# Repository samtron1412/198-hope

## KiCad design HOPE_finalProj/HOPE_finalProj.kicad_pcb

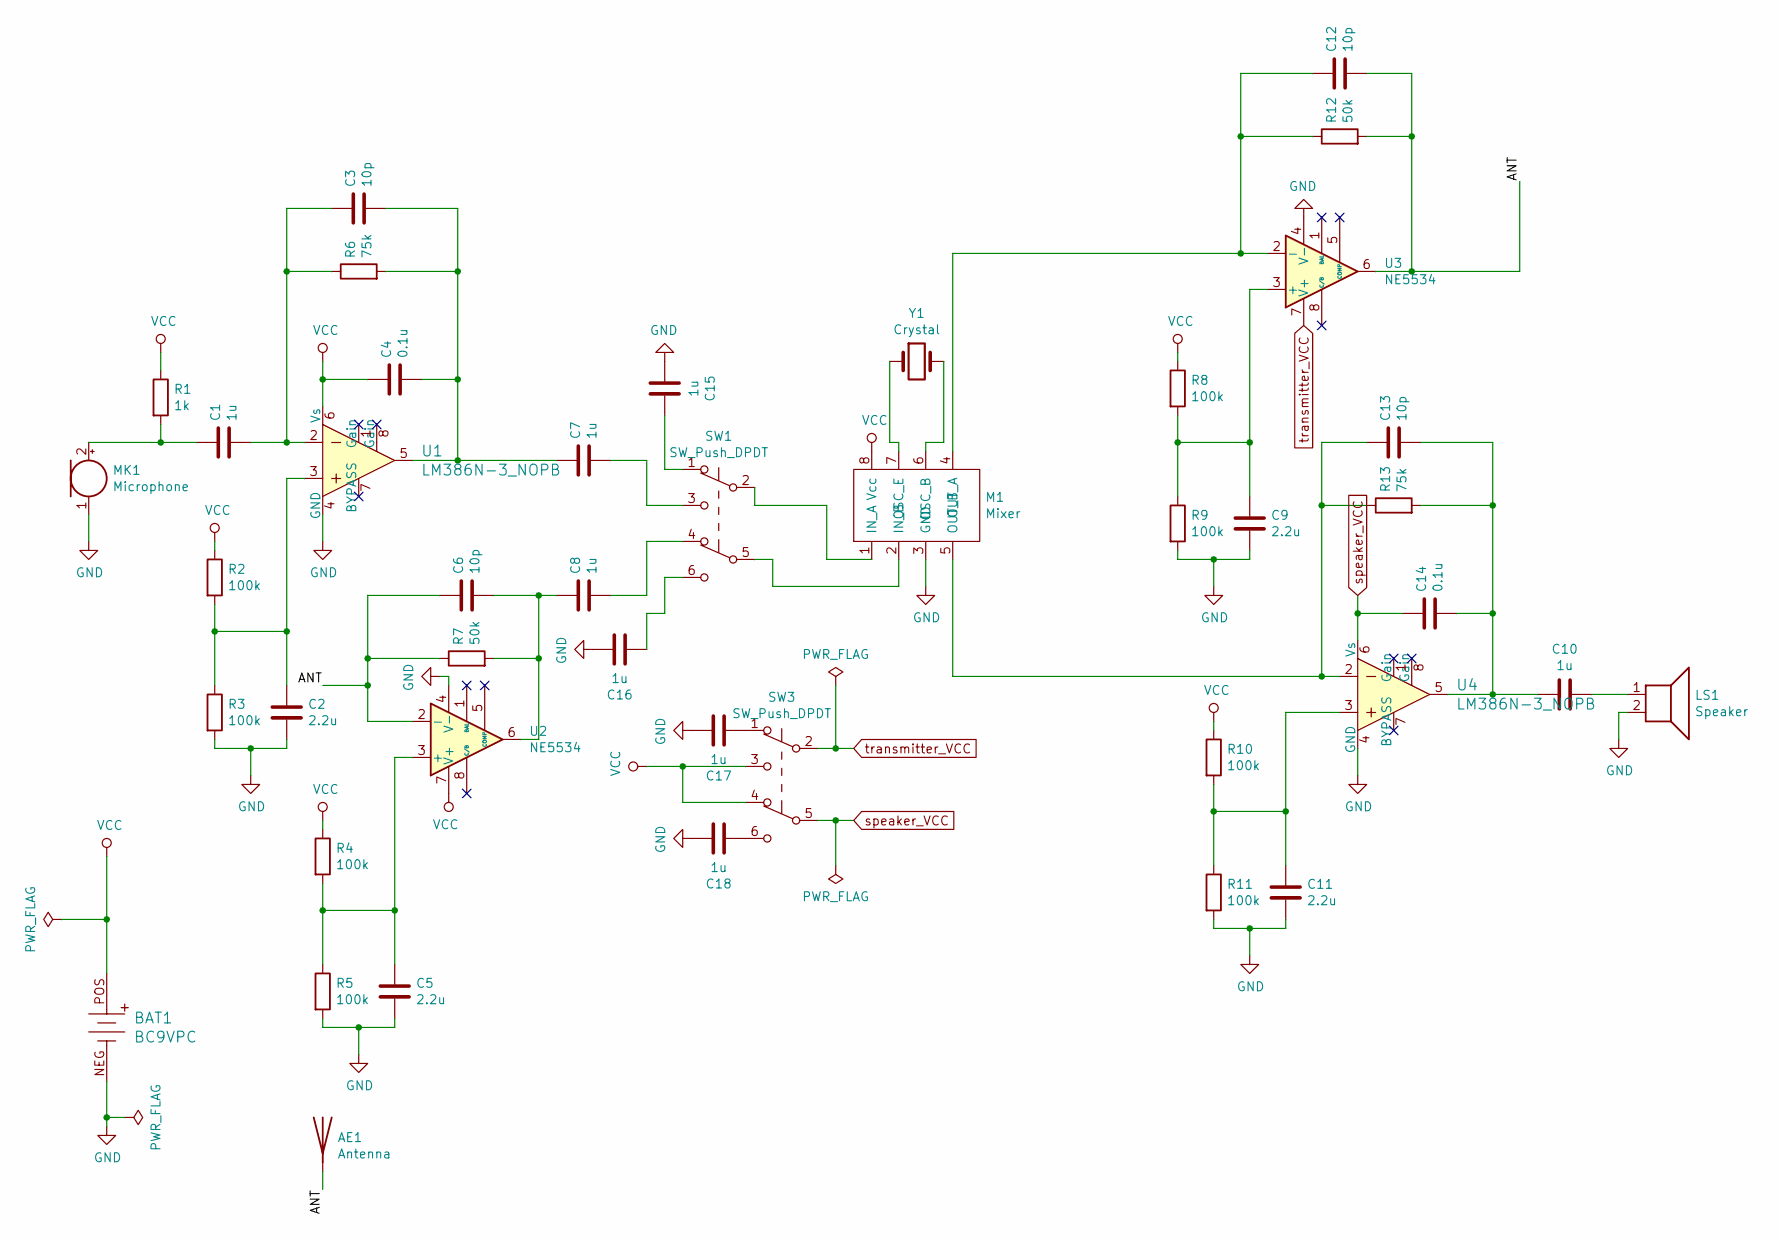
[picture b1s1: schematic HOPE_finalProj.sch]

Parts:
AE1: Antenna; Antena
BAT1: BC9VPC; Battery_Holder_9V_BC9VPC-ND; MPN BC9VPC; Digi-Key_PN BC9VPC-ND
C1, C7, C8, C10, C15, C16, C17, C18: 1u; C_Disc_D3.0mm_W1.6mm_P2.50mm
C2, C5, C9, C11: 2.2u; C_Disc_D3.0mm_W1.6mm_P2.50mm
C3, C6, C12, C13: 10p; C_Disc_D5.0mm_W2.5mm_P2.50mm
C4, C14: 0.1u; C_Disc_D3.0mm_W1.6mm_P2.50mm
LS1: Speaker; SolderWirePad_1x02_P3.81mm_Drill0.8mm
M1: Mixer; DIP-8_W7.62mm
MK1: Microphone; Mic
R1: 1k; R_Axial_DIN0204_L3.6mm_D1.6mm_P7.62mm_Horizontal
R2, R3, R4, R5, R8, R9, R10, R11: 100k; R_Axial_DIN0204_L3.6mm_D1.6mm_P7.62mm_Horizontal
R6, R13: 75k; R_Axial_DIN0204_L3.6mm_D1.6mm_P7.62mm_Horizontal
R7, R12: 50k; R_Axial_DIN0207_L6.3mm_D2.5mm_P10.16mm_Horizontal
SW1, SW3: SW_Push_DPDT; DPDT_Switch
U1, U4: LM386N-3_NOPB; DIP-8_W7.62mm; MPN LM386N-3/NOPB; Digi-Key_PN 296-43959-5-ND
U2, U3: NE5534; DIP-8_W7.62mm
Y1: Crystal

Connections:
/ANT: AE1.1, C6.1, C12.2, R7.1, R12.2, U2.2 (-), U3.6
GND: BAT1.NEG, C2.2, C5.2, C9.2, C11.2, C15.2, C16.1, C17.1, C18.1, LS1.2, M1.3 (GND), MK1.1 (-), R3.2, R5.2, R9.2, R11.2, U1.4 (GND), U2.4 (V-), U3.4 (V-), U4.4 (GND)
unnamed: C1.1, MK1.2 (+), R1.2
unnamed: C1.2, C3.1, R6.1, U1.2
unnamed: C2.1, R2.2, R3.1, U1.3
unnamed: C3.2, C4.2, C7.1, R6.2, U1.5
unnamed: C5.1, R4.2, R5.1, U2.3 (+)
unnamed: C6.2, C8.1, R7.2, U2.6
unnamed: C7.2, SW1.3 (C)
unnamed: C8.2, SW1.4 (A)
unnamed: C9.1, R8.2, R9.1, U3.3 (+)
unnamed: C10.1, LS1.1
unnamed: C10.2, C13.2, C14.2, R13.2, U4.5
unnamed: C11.1, R10.2, R11.1, U4.3
unnamed: C12.1, M1.4 (OUT_A), R12.1, U3.2 (-)
unnamed: C13.1, M1.5 (OUT_B), R13.1, U4.2
unnamed: C15.1, SW1.1 (A)
unnamed: C16.2, SW1.6 (C)
unnamed: C17.2, SW3.1 (A)
unnamed: C18.2, SW3.6 (C)
unnamed: M1.1 (IN_A), SW1.2 (B)
unnamed: M1.2 (IN_B), SW1.5 (B)
unnamed: M1.6 (OSC_B), Y1.2
unnamed: M1.7 (OSC_E), Y1.1
VCC: BAT1.POS, C4.1, M1.8 (Vcc), R1.1, R2.1, R4.1, R8.1, R10.1, SW3.3 (C), SW3.4 (A), U1.6 (Vs), U2.7 (V+)
speaker_VCC: C14.1, SW3.5 (B), U4.6 (Vs)
transmitter_VCC: SW3.2 (B), U3.7 (V+)

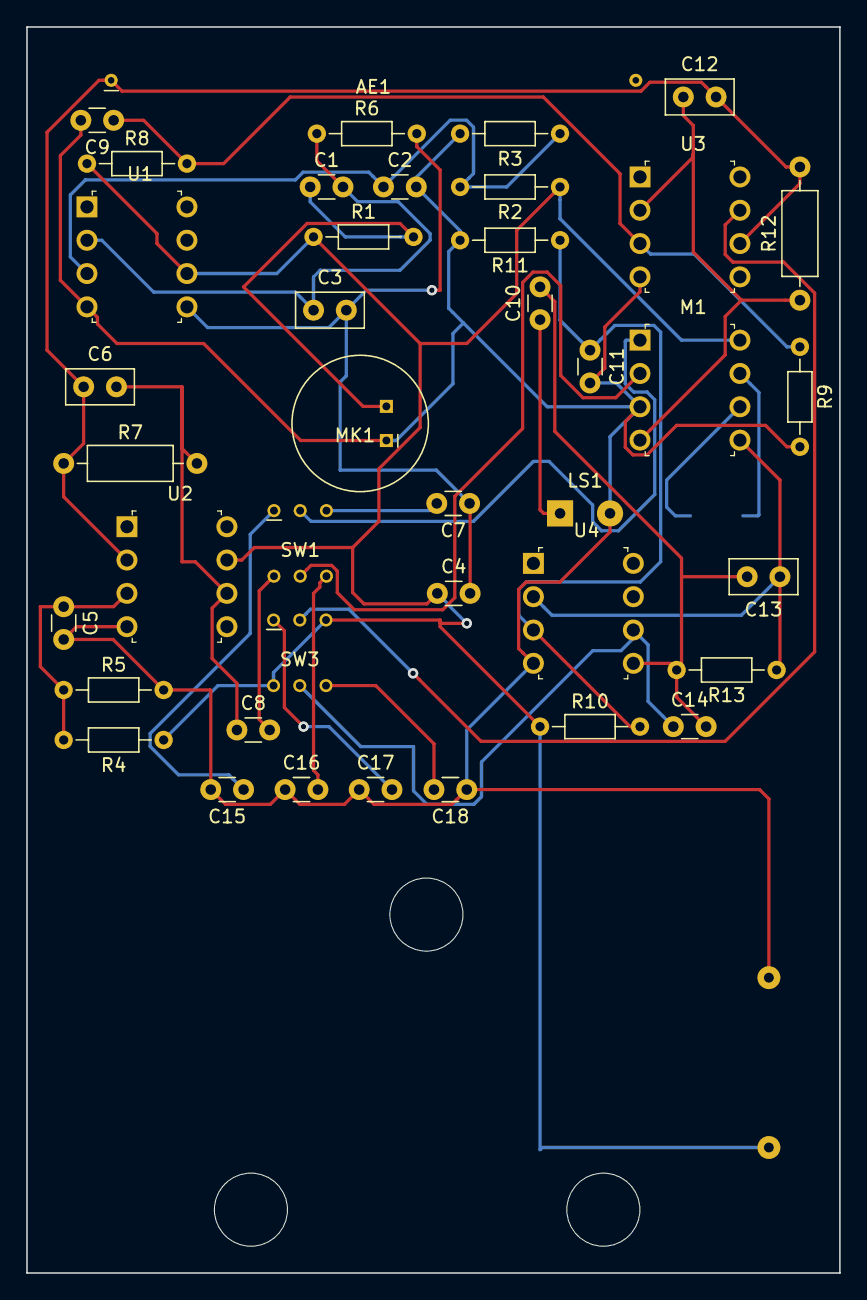
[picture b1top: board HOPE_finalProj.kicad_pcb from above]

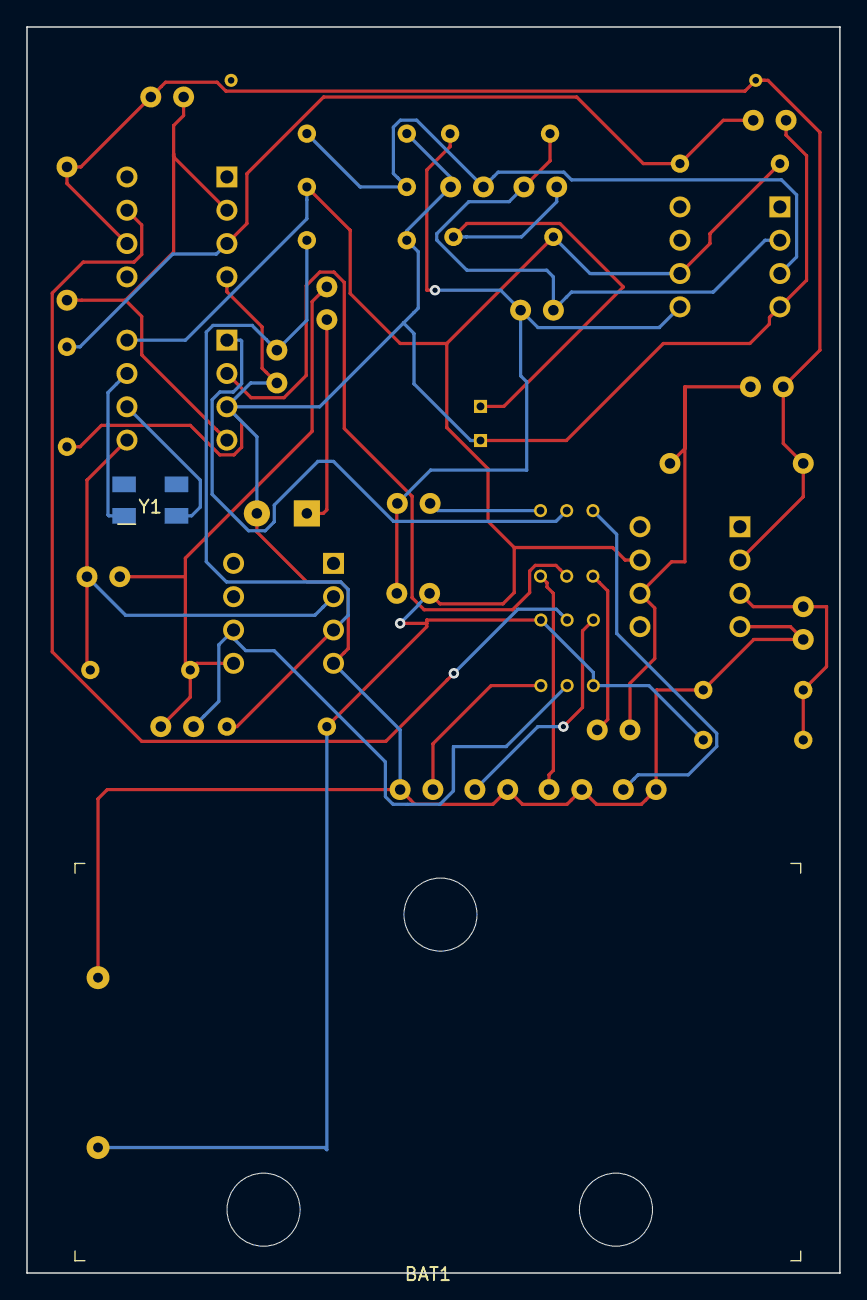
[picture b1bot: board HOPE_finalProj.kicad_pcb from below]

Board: 2 copper layers, 62.0 x 95.0 mm, 43 parts (2 on the bottom side), 27 nets.

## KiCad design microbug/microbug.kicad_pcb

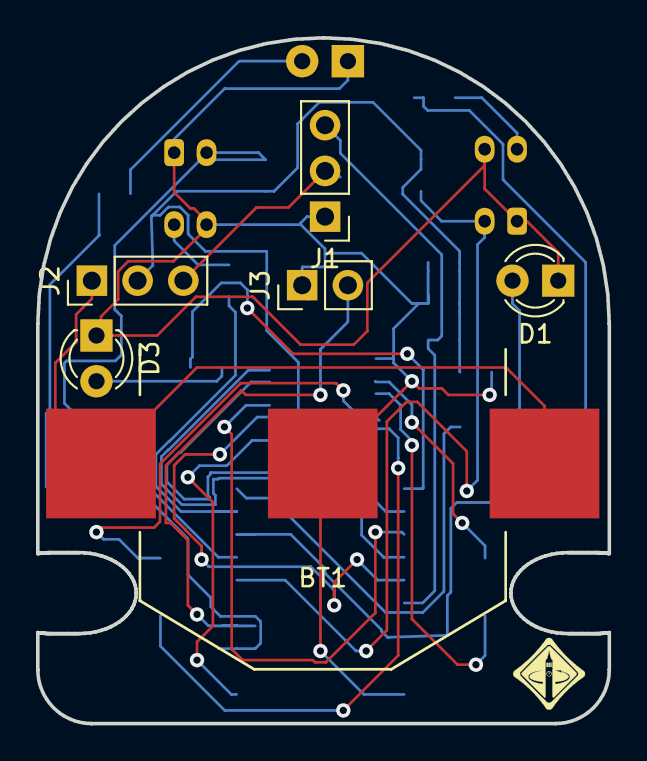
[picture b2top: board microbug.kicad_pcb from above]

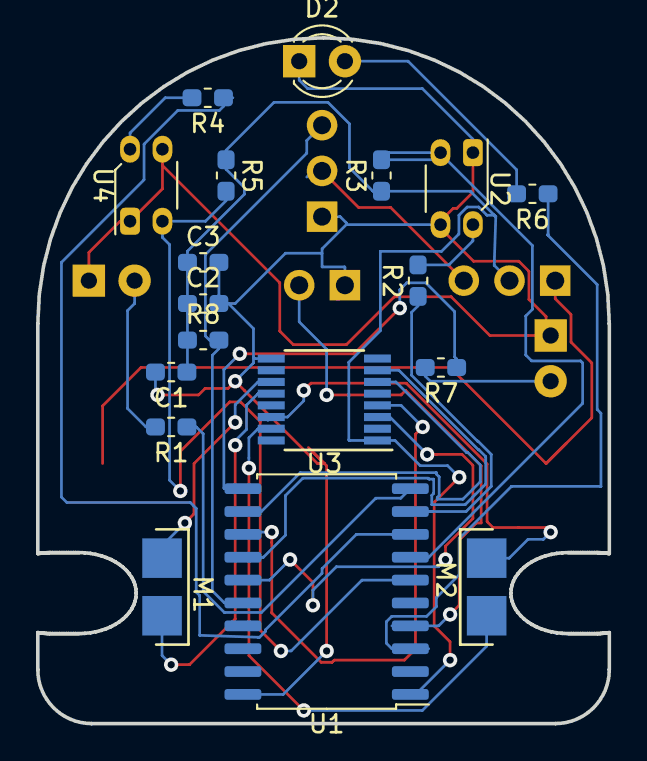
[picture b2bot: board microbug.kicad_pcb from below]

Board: 2 copper layers, 31.7 x 38.1 mm, 24 parts (18 on the bottom side), 26 nets.

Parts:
BT1: Battery_Cell; BK-883
C1: 0.1u; C_0603_1608Metric_Pad1.05x0.95mm_HandSolder
C2: 1u; C_0603_1608Metric_Pad1.05x0.95mm_HandSolder
C3: 10u; C_0603_1608Metric_Pad1.05x0.95mm_HandSolder
D1, D2, D3: LED; LED_D3.0mm
J1, J2: Conn_01x03; PinHeader_1x03_P2.54mm_Vertical
J3: Conn_01x02; PinHeader_1x02_P2.54mm_Vertical
M1, M2: Motor_DC; micro_motor_5mm
R1, R6, R7: 220; R_0603_1608Metric_Pad1.05x0.95mm_HandSolder
R2, R4: 100; R_0603_1608Metric_Pad1.05x0.95mm_HandSolder
R3, R5, R8: 10k; R_0603_1608Metric_Pad1.05x0.95mm_HandSolder
U1: ATtiny1616-S; SOIC-20W_7.5x12.8mm_P1.27mm
U2, U4: QRE1113GR; Everlight_ITR8307F43
U3: TC78H651AFNG; TSSOP-16_4.4x5mm_P0.65mm

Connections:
+3V3: C1.1, C2.1, C3.1, J2.2, R3.1, R5.1, R8.1, U1.1, U3.1
/DAC: J3.2, U1.4
/DIR1: U1.14, U3.7
/DIR2: U1.15, U3.3
/IR1: R2.1, U1.9
/IR2: R4.1, U1.8
/LED1: R1.1, U1.10
/LED2: R6.1, U1.3
/LED3: R7.1, U1.11
/OUT1: R3.2, U1.7, U2.3
/OUT2: R5.2, U1.6, U4.3
/PWM1: U1.12, U3.6
/PWM2: U1.13, U3.4
/UDPI: J1.3, R8.2, U1.16
GND: BT1.2, C1.2, C2.2, C3.2, D1.1, D2.1, D3.1, J1.1, J3.1, U1.20, U2.1, U2.4, U3.9, U4.1, U4.4
unnamed: BT1.1, J2.1
unnamed: D1.2, R1.2
unnamed: D2.2, R6.2
unnamed: D3.2, R7.2
unnamed: J1.2, J2.3
unnamed: M1.1, U3.11
unnamed: M1.2, U3.12
unnamed: M2.1, U3.15
unnamed: M2.2, U3.14
unnamed: R2.2, U2.2
unnamed: R4.2, U4.2

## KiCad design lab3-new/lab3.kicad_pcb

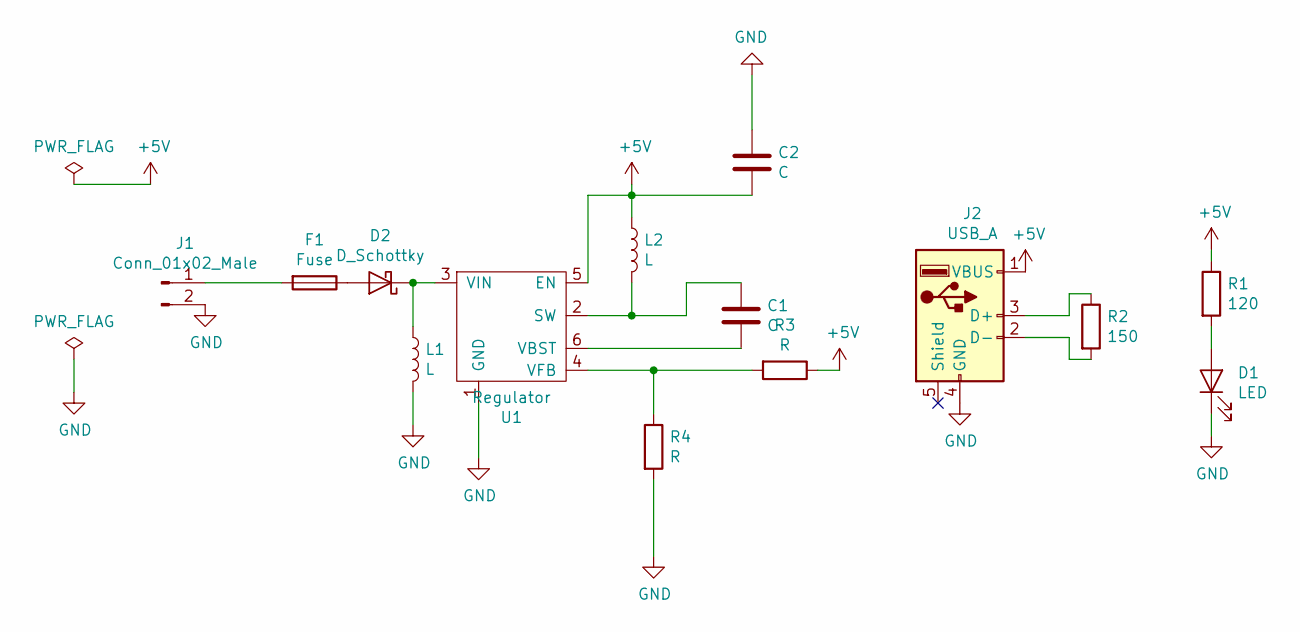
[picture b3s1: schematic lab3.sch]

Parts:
C1, C2: C; C_Disc_D3.0mm_W1.6mm_P2.50mm
D1: LED; led
D2: D_Schottky; diode2
F1: Fuse; Fuse_BelFuse_0ZRE0005FF_L8.3mm_W3.8mm
J1: Conn_01x02_Male; JWT_A3963_1x02_P3.96mm_Vertical
J2: USB_A; USB_A_CNCTech_1001-011-01101_Horizontal
L1, L2: L; L_Axial_L5.0mm_D3.6mm_P10.00mm_Horizontal_Murata_BL01RN1A2A2
R1: 120; R_Axial_DIN0204_L3.6mm_D1.6mm_P1.90mm_Vertical
R2: 150; R_Axial_DIN0204_L3.6mm_D1.6mm_P1.90mm_Vertical
R3, R4: R; R_Axial_DIN0204_L3.6mm_D1.6mm_P1.90mm_Vertical
U1: Regulator; regulator

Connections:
+5V: C2.2, J2.1 (VBUS), L2.1, R1.1, R3.1, U1.5 (EN)
GND: C2.1, D1.1 (K), J1.2, J2.4 (GND), L1.2, R4.2, U1.1 (GND)
unnamed: C1.1, L2.2, U1.2 (SW)
unnamed: C1.2, U1.6 (VBST)
unnamed: D1.2 (A), R1.2
unnamed: D2.1 (K), L1.1, U1.3 (VIN)
unnamed: D2.2 (A), F1.1
unnamed: F1.2, J1.1
unnamed: J2.2 (D-), R2.2
unnamed: J2.3 (D+), R2.1
unnamed: R3.2, R4.1, U1.4 (VFB)

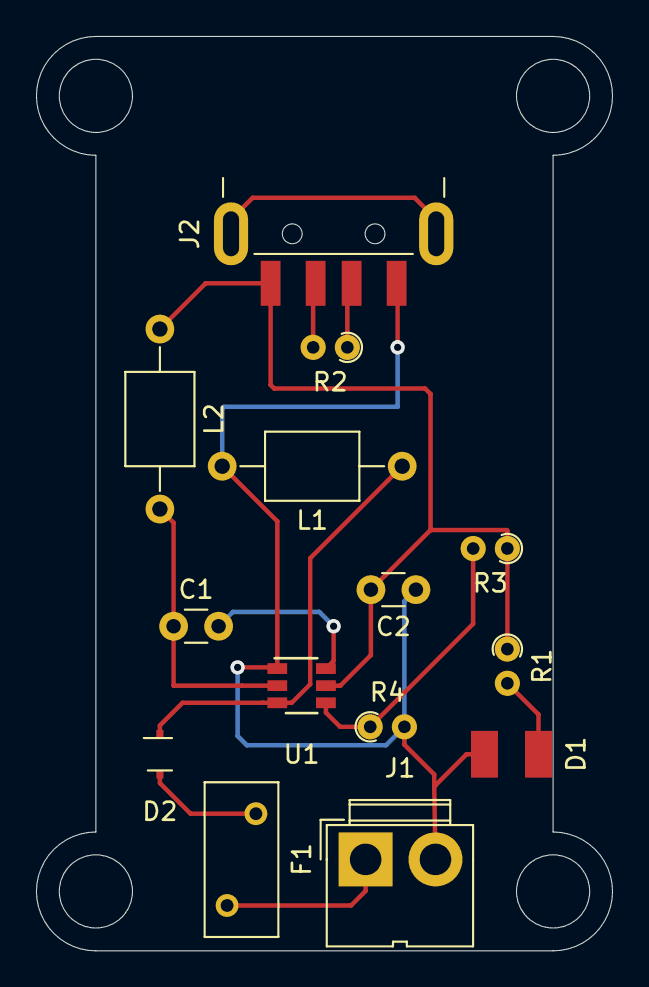
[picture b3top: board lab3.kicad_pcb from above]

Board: 2 copper layers, 32.0 x 50.8 mm, 14 parts (0 on the bottom side), 11 nets.

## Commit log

2020-02-29 Ignore macos stuff
2020-02-29 add footprint for diode(unfinished)
2020-02-29 add diode footprint
2020-02-29 Add led footprint
2020-02-29 Add libraries
2020-03-01 Finished footprint creation and board setup
2020-03-01 smd to tht
2020-03-01 Finished layout
2020-03-11 changed diode footprint and assigned to schematic
2020-03-11 updated diode in layout
2020-03-12 updated connectors
2020-03-12 finished circuit
2020-03-12 final project deliverables
2020-03-12 added bom
2020-04-01 Add final project
2020-04-01 remove library
2020-04-01 added Digikey library
2020-04-01 Completed sch
2020-04-01 Added some footprint
2020-04-02 Finished footprint
2020-04-02 fixed sch
2020-04-08 microbug
2020-04-09 some layout done
2020-04-09 almost done
2020-04-09 finished
2020-04-09 microbug finished
2020-04-09 removed weird file
2020-04-09 Remove project.zip
2020-04-09 added logo
2020-04-16 Layout finished
2020-04-16 Fixed battery
2020-04-21 Changes in the OH
2020-04-29 Add a TPDT switch
2020-04-29 Add switches for transmitter and speaker
2020-04-30 Doing layout
2020-04-30 fixed unconnected components
2020-04-30 bigger hole
2020-04-30 bigger?
2020-04-30 fixed hole sizes
2020-04-30 Change 10pF capacitors: cheaper and smaller

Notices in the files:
lab3-new/lab3.kicad_pcb:
License: CC BY 4.0
